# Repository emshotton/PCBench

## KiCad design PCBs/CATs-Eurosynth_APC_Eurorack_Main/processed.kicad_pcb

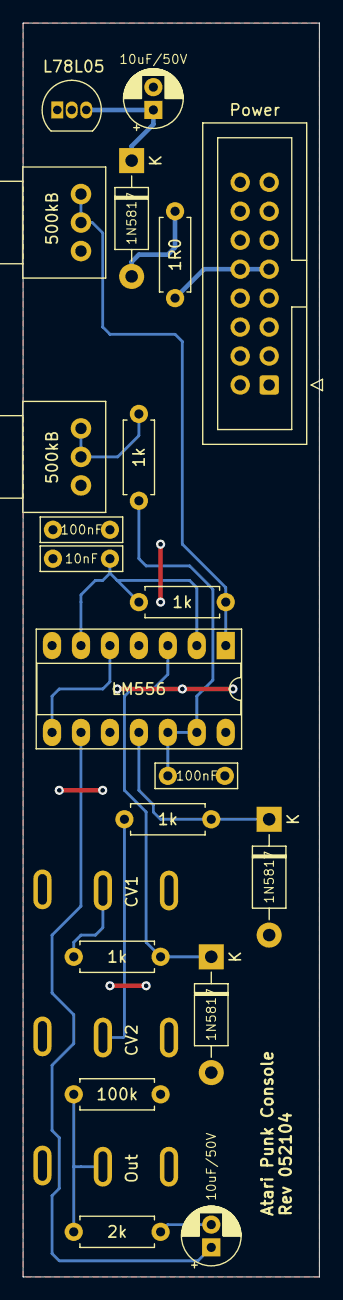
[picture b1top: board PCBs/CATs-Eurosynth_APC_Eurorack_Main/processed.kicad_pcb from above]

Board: 2 copper layers, 26.0 x 110.0 mm, 23 parts (0 on the bottom side), 17 nets.

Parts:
C1: 10nF; C_Rect_L7.0mm_W2.0mm_P5.00mm
C2, C4: 100nF; C_Rect_L7.0mm_W2.0mm_P5.00mm
C3, C5: 10uF/50V; CP_Radial_D5.0mm_P2.00mm
D1, D2, D3: 1N5817; D_DO-41_SOD81_P10.16mm_Horizontal
IC1: L78L05; TO-92_Inline
IC2: LM556; DIP-14_W7.62mm_Socket_LongPads
J1: Power; IDC-Header_2x08_P2.54mm_Vertical
J4: Out; PJ-323
J5: CV2; PJ-323
J6: CV1; PJ-323
R1, R7, R8, R9: 1k; R_Axial_DIN0207_L6.3mm_D2.5mm_P7.62mm_Horizontal
R2: 1R0; R_Axial_DIN0207_L6.3mm_D2.5mm_P7.62mm_Horizontal
R3: 100k; R_Axial_DIN0207_L6.3mm_D2.5mm_P7.62mm_Horizontal
R4: 2k; R_Axial_DIN0207_L6.3mm_D2.5mm_P7.62mm_Horizontal
R10, R11: 500kB; Potentiometer_Alps_RK097_Single_Horizontal

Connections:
+12V: J1.9, J1.10, R2.2
+VDC: C4.1, IC1.1, IC2.4, IC2.10, IC2.14, R10.3, R11.3
GND: C1.2, C2.2, C4.2, C5.2, D2.2, D3.2, IC1.2, IC2.7, J1.3, J1.4, J1.5, J1.6, J1.7, J1.8, J4.S, J5.S, J6.S, R3.1
unnamed: C1.1, IC2.2, IC2.6, R1.2
unnamed: C2.1, IC2.12, IC2.13, R9.1
unnamed: C3.1, IC2.9
unnamed: C3.2, R4.2
unnamed: C5.1, D1.1, IC1.3
unnamed: D1.2, R2.1
unnamed: D2.1, IC2.3, R7.2
unnamed: D3.1, IC2.11, R8.2
unnamed: IC2.1, R1.1, R10.1, R10.2
unnamed: IC2.5, IC2.8
unnamed: J4.T, R3.2, R4.1
unnamed: J5.T, R8.1
unnamed: J6.T, R7.1
unnamed: R9.2, R11.1, R11.2

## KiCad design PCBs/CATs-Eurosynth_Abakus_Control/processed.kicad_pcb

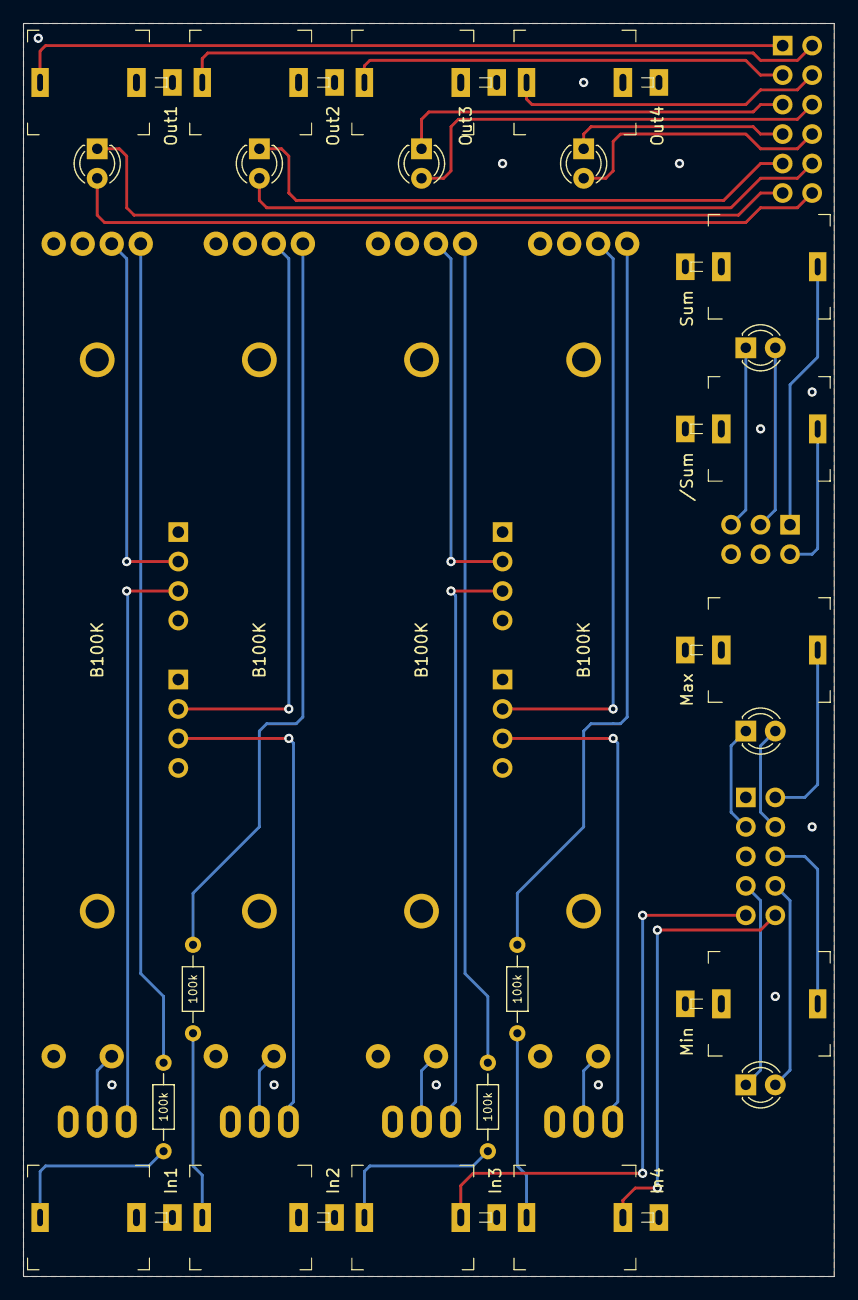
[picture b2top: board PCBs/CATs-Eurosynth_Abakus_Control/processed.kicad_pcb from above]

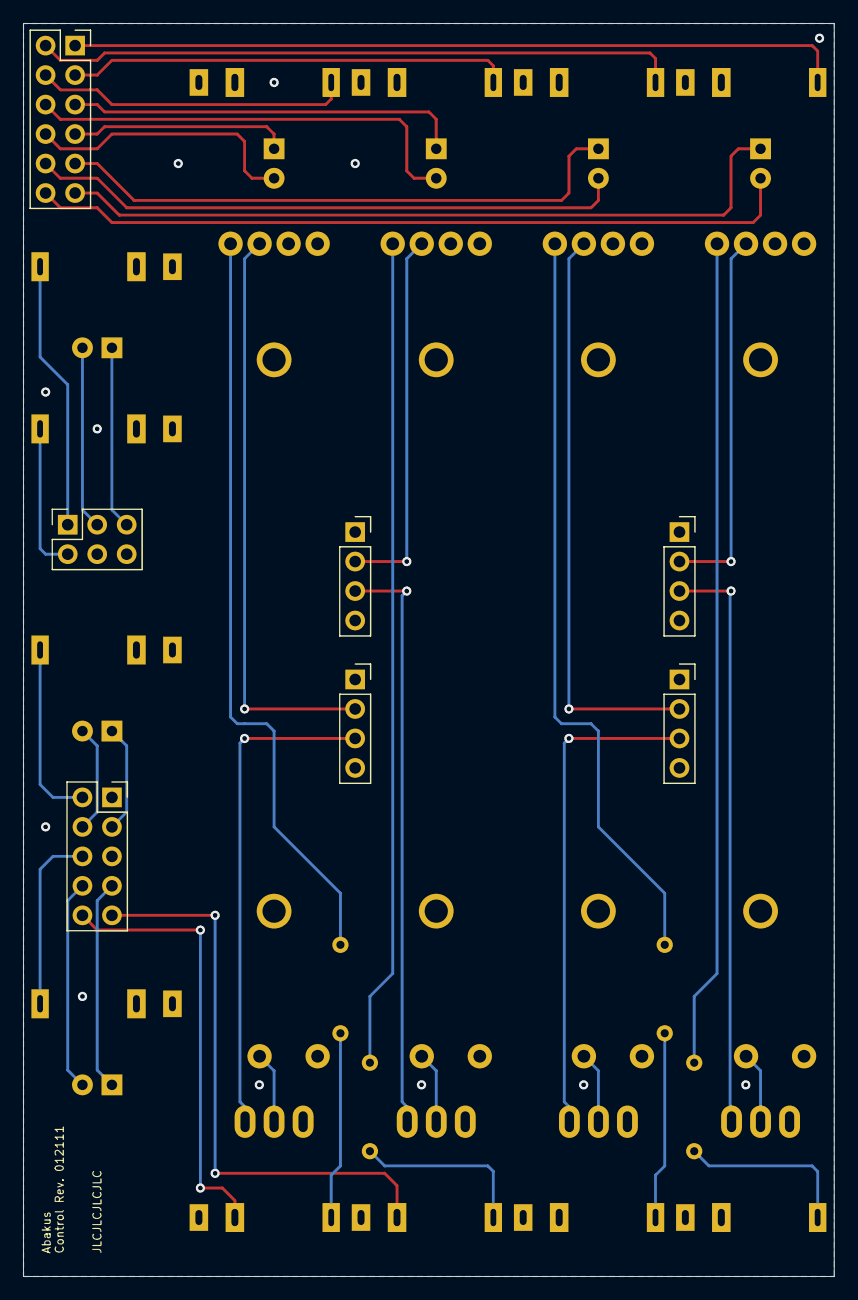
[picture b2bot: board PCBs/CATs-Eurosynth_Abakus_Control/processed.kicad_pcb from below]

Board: 2 copper layers, 69.8 x 108.0 mm, 38 parts (7 on the bottom side), 45 nets.

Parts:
D1: Out1; LED_D3.0mm
D2: Out2; LED_D3.0mm
D3: Out3; LED_D3.0mm
D4: Out4; LED_D3.0mm
D5: Min; LED_D3.0mm
D6: Sum; LED_D3.0mm
D7: Max; LED_D3.0mm
J1: In1; Jack_3.5mm_QingPu_WQP-PJ301M-12
J2: In2; Jack_3.5mm_QingPu_WQP-PJ301M-12
J3: In3; Jack_3.5mm_QingPu_WQP-PJ301M-12
J4: In4; Jack_3.5mm_QingPu_WQP-PJ301M-12
J5: Out1; Jack_3.5mm_QingPu_WQP-PJ301M-12
J6: Out2; Jack_3.5mm_QingPu_WQP-PJ301M-12
J7: Out3; Jack_3.5mm_QingPu_WQP-PJ301M-12
J8: Out4; Jack_3.5mm_QingPu_WQP-PJ301M-12
J9: /Sum; Jack_3.5mm_QingPu_WQP-PJ301M-12
J10: Sum; Jack_3.5mm_QingPu_WQP-PJ301M-12
J11: Max; Jack_3.5mm_QingPu_WQP-PJ301M-12
J12: Min; Jack_3.5mm_QingPu_WQP-PJ301M-12
J13: Out; PinSocket_2x06_P2.54mm_Vertical
J14: In1; PinSocket_1x04_P2.54mm_Vertical
J15: In2; PinSocket_1x04_P2.54mm_Vertical
J16: In3; PinSocket_1x04_P2.54mm_Vertical
J17: In4; PinSocket_1x04_P2.54mm_Vertical
J18: Sum; PinSocket_2x03_P2.54mm_Vertical
J19: MinMax; PinSocket_2x05_P2.54mm_Vertical
P1, P2, P3, P4: B100K; Potentiometer_AlpsAlpine_RS6011YA9A07
R1, R2, R3, R4: 100k; R_Axial_DIN0204_L3.6mm_D1.6mm_P7.62mm_Horizontal
SW1: Att/AV1; SMTS-102-2xxx
SW2: Att/AV2; SMTS-102-2xxx
SW3: Att/AV3; SMTS-102-2xxx
SW4: Att/AV4; SMTS-102-2xxx

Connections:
+5V: J3.TN, J19.9
+10V: J4.TN, J19.10
+In1: J14.2, P1.CW
+In2: J15.2, P2.CW
+In3: J16.2, P3.CW
+In4: J17.2, P4.CW
-In1: J14.3, SW1.1
-In2: J15.3, SW2.1
-In3: J16.3, SW3.1
-In4: J17.3, SW4.1
GND: J1.S, J1.TN, J2.S, J2.TN, J3.S, J4.S, J5.S, J6.S, J7.S, J8.S, J9.S, J10.S, J11.S, J12.S, J14.1, J14.4, J15.1, J15.4, J16.1, J16.4, J17.1, J17.4, J18.4, J18.6, J19.1, J19.5, SW1.3, SW2.3, SW3.3, SW4.3
Inv_Sum: J9.T, J18.2
LED_Max_1: D7.1, J19.3
LED_Max_2: D7.2, J19.4
LED_Min_1: D5.1, J19.7
LED_Min_2: D5.2, J19.8
LED_Out_1_1: D1.1, J13.11
LED_Out_1_2: D1.2, J13.12
LED_Out_2_1: D2.1, J13.9
LED_Out_2_2: D2.2, J13.10
LED_Out_3_1: D3.1, J13.5
LED_Out_3_2: D3.2, J13.6
LED_Out_4_1: D4.1, J13.7
LED_Out_4_2: D4.2, J13.8
LED_Sum_1: D6.1, J18.5
LED_Sum_2: D6.2, J18.3
Max: J11.T, J19.2
Min: J12.T, J19.6
unnamed: J1.T, R1.2
unnamed: J2.T, R2.2
unnamed: J3.T, R3.2
unnamed: J4.T, R4.2
unnamed: P1.CCW, SW1.2
unnamed: P1.W, R1.1
unnamed: P2.CCW, SW2.2
unnamed: P2.W, R2.1
unnamed: P3.CCW, SW3.2
unnamed: P3.W, R3.1
unnamed: P4.CCW, SW4.2
unnamed: P4.W, R4.1
Out1: J5.T, J13.1
Out2: J6.T, J13.2
Out3: J7.T, J13.3
Out4: J8.T, J13.4
Sum: J10.T, J18.1

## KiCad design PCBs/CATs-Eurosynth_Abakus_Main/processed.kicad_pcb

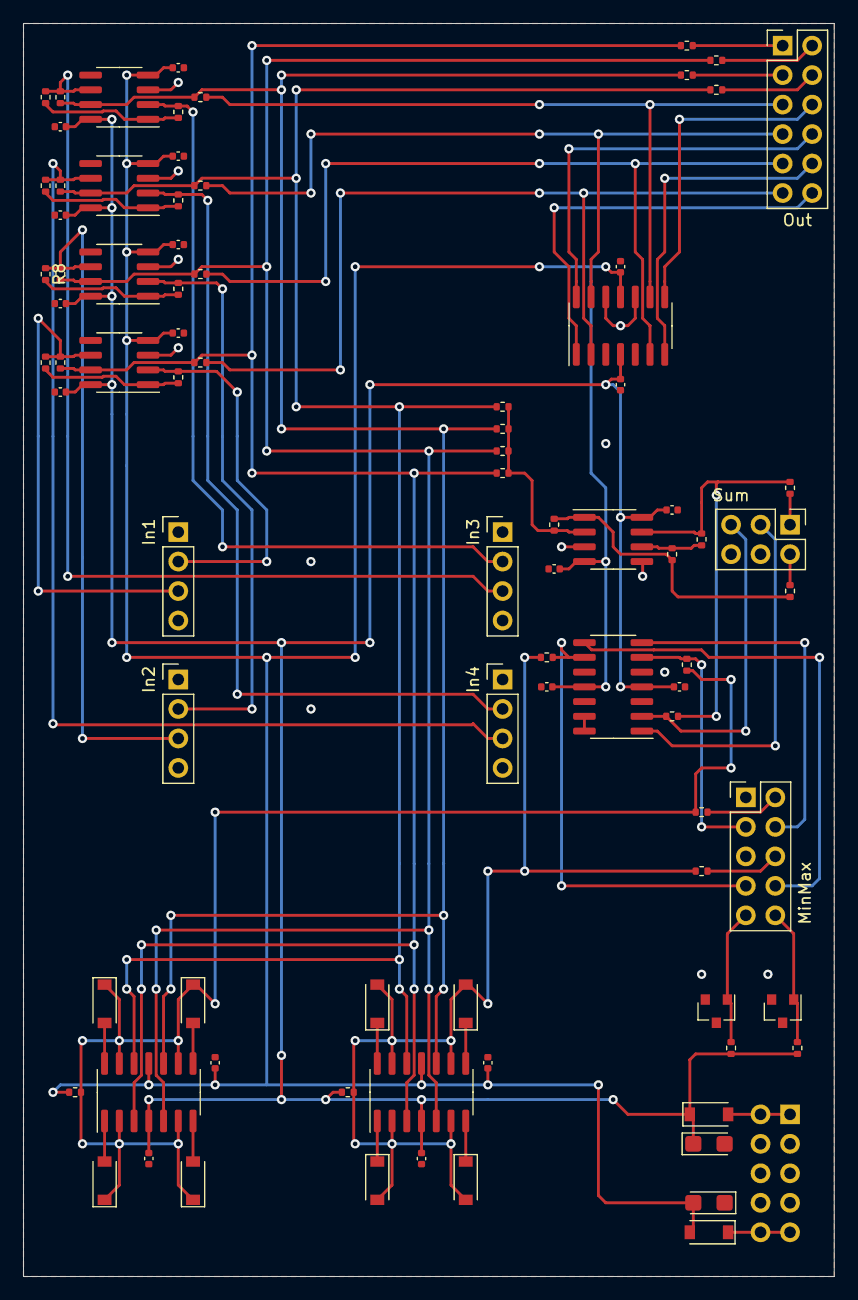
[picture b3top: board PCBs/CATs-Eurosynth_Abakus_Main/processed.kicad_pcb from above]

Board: 2 copper layers, 69.8 x 108.0 mm, 87 parts (1 on the bottom side), 60 nets.

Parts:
C1, C2: 10µ; CP_EIA-3216-18_Kemet-A
C3, C4, C5, C6, C7, C8, C9, C10, C11, C12, C13, C14, C15, C16, C17, C18, C19, C20: 100n; C_0402_1005Metric
D1, D2: B5817W; D_SOD-123
D3, D4, D5, D6, D7, D8, D9, D10: 1N4148W; D_SOD-123
J1: Power; Power_2x5_Vertical
J2: Out; PinHeader_2x06_P2.54mm_Vertical
J3: In1; PinHeader_1x04_P2.54mm_Vertical
J4: In2; PinHeader_1x04_P2.54mm_Vertical
J5: In3; PinHeader_1x04_P2.54mm_Vertical
J6: In4; PinHeader_1x04_P2.54mm_Vertical
J7: Sum; PinHeader_2x03_P2.54mm_Vertical
J8: MinMax; PinHeader_2x05_P2.54mm_Vertical
R1, R2, R3, R4, R7, R8, R9, R10, R11, R12, R13, R14, R21, R22, R23, R24, R27, R29, R30: 100k; R_0402_1005Metric
R5, R6, R15, R16, R17, R18, R19, R20, R25, R26, R28, R31, R32, R34, R36, R37, R38: 1k; R_0402_1005Metric
R33, R35: 10k; R_0402_1005Metric
U1, U2, U3, U4, U5: TL072CDT; SOIC-8_3.9x4.9mm_P1.27mm
U6, U7, U8, U9: TL074CDR; SOIC-14_3.9x8.7mm_P1.27mm
U10: LM4040AIM3-5.0/NOPB; SOT-23
U11: LM4040C10IDBZR; SOT-23

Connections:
+5V: J8.9, R37.1, U10.1
+10V: J8.10, R38.1, U11.1
+12V: C1.1, C3.1, C5.1, C7.1, C9.1, C11.1, C13.1, C15.1, C17.1, C19.1, D1.1, R35.2, R37.2, R38.2, U1.8, U2.8, U3.8, U4.8, U5.8, U6.4, U7.4, U8.4, U9.4
+In1: J3.2, R1.2, U1.2
+In2: J4.2, R2.2, U2.2
+In3: J5.2, R3.2, U3.2
+In4: J6.2, R4.2, U4.2
-12V: C2.2, C4.2, C6.2, C8.2, C10.2, C12.2, C14.2, C16.2, C18.2, C20.2, D2.2, R33.1, U1.4, U2.4, U3.4, U4.4, U5.4, U6.11, U7.11, U8.11, U9.11
-In1: J3.3, R7.1, R11.2, U1.6
-In2: J4.3, R8.1, R12.2, U2.6
-In3: J5.3, R9.1, R13.2, U3.6
-In4: J6.3, R10.1, R14.2, U4.6
GND: C1.2, C2.1, C3.2, C4.1, C5.2, C6.1, C7.2, C8.1, C9.2, C10.1, C11.2, C12.1, C13.2, C14.1, C15.2, C16.1, C17.2, C18.1, C19.2, C20.1, J1.GND, J3.1, J3.4, J4.1, J4.4, J5.1, J5.4, J6.1, J6.4, J7.4, J7.6, J8.1, J8.5, U1.3, U1.5, U2.3, U2.5, U3.3, U3.5, U4.3, U4.5, U5.3, U5.5, U8.3, U8.5, U8.10, U8.12, U9.3, U9.5, U9.10, U9.12, U10.2, U11.2
Int_Inv_Sum: R27.1, R28.2, R29.2, U5.1
Int_Max: D3.1, D4.1, D5.1, D6.1, R31.2, R33.2, R34.2, U6.2, U6.6, U6.9, U6.13
Int_Min: D7.2, D8.2, D9.2, D10.2, R26.2, R35.1, R36.2, U7.2, U7.6, U7.9, U7.13
Int_Out1: R5.2, R11.1, R17.2, R21.2, U1.7, U6.3, U7.3
Int_Out2: R12.1, R15.2, R18.2, R22.2, U2.7, U6.5, U7.5
Int_Out3: R6.2, R13.1, R19.2, R23.2, U3.7, U6.10, U7.10
Int_Out4: R14.1, R16.2, R20.2, R24.2, U4.7, U6.12, U7.12
Int_Sum: R25.2, R30.1, R32.2, U5.7
Inv_Sum: J7.2, R28.1
LED_Max_1: J8.3, R31.1, U9.6
LED_Max_2: J8.4, U9.7
LED_Min_1: J8.7, R26.1, U9.9
LED_Min_2: J8.8, U9.8
LED_Out_1_1: J2.11, R5.1, U8.2
LED_Out_1_2: J2.12, U8.1
LED_Out_2_1: J2.9, R15.1, U8.6
LED_Out_2_2: J2.10, U8.7
LED_Out_3_1: J2.5, R6.1, U8.9
LED_Out_3_2: J2.6, U8.8
LED_Out_4_1: J2.7, R16.1, U8.13
LED_Out_4_2: J2.8, U8.14
LED_Sum_1: J7.5, R25.1, U9.2
LED_Sum_2: J7.3, U9.1
Max: J8.2, R34.1
Min: J8.6, R36.1
unnamed: D1.2, J1.+12V
unnamed: D2.1, J1.-12V
unnamed: D3.2, U6.1
unnamed: D4.2, U6.7
unnamed: D5.2, U6.8
unnamed: D6.2, U6.14
unnamed: D7.1, U7.1
unnamed: D8.1, U7.7
unnamed: D9.1, U7.8
unnamed: D10.1, U7.14
unnamed: R1.1, R7.2, U1.1
unnamed: R2.1, R8.2, U2.1
unnamed: R3.1, R9.2, U3.1
unnamed: R4.1, R10.2, U4.1
unnamed: R21.1, R22.1, R23.1, R24.1, R27.2, U5.2
unnamed: R29.1, R30.2, U5.6
unnamed: U9.13, U9.14
Out1: J2.1, R17.1
Out2: J2.2, R18.1
Out3: J2.3, R19.1
Out4: J2.4, R20.1
Sum: J7.1, R32.1

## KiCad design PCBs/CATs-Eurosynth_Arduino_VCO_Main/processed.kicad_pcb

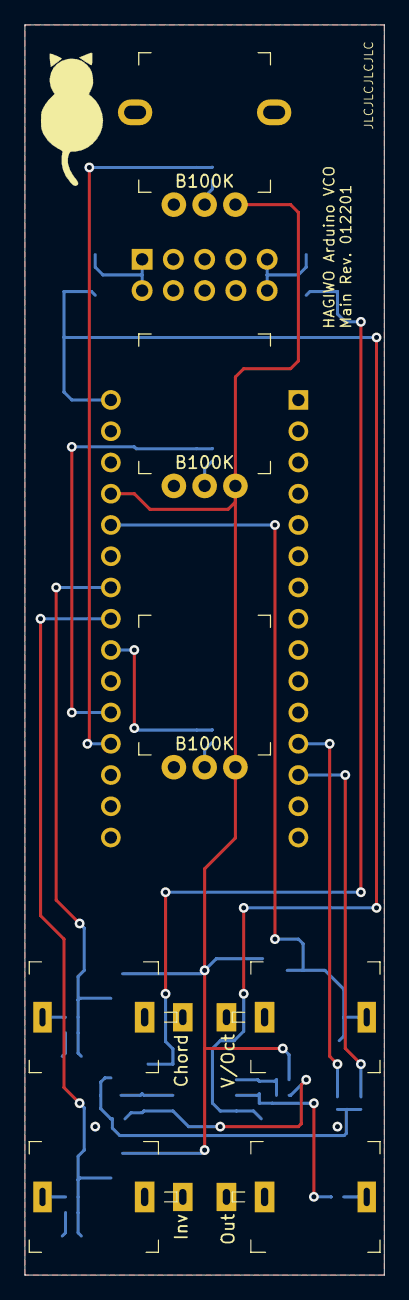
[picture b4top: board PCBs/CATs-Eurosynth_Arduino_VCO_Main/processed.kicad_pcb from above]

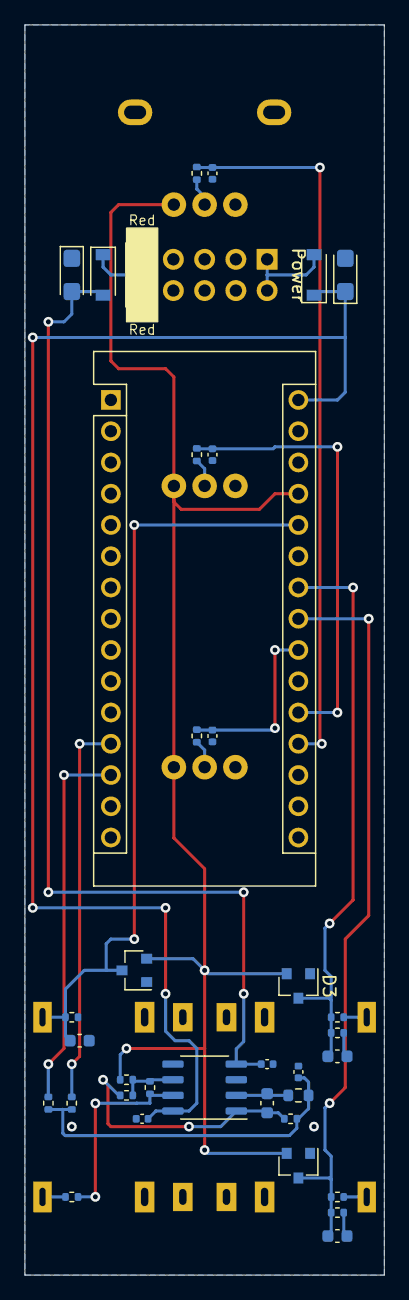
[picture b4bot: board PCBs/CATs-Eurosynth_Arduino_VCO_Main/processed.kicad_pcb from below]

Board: 2 copper layers, 29.2 x 101.6 mm, 43 parts (36 on the bottom side), 25 nets.

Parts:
A1: Arduino_Nano_v3.x; Arduino_Nano
C1, C11: 10µ; CP_EIA-3216-18_Kemet-A
C2, C3, C4: 10n; C_0402_1005Metric
C5, C7, C9: 68n; C_0603_1608Metric
C6: 3.3n; C_0603_1608Metric
C8: 22n; C_0402_1005Metric
C10, C12: 100n; C_0402_1005Metric
D1, D6: B5819W SL; D_SOD-123
D2, D3, D4: BAV99; SOT-23
J1: Power; Power_2x5_Vertical
J2: V/Oct; Jack_3.5mm_QingPu_WQP-PJ301M-12
J3: Inv; Jack_3.5mm_QingPu_WQP-PJ301M-12
J4: Out; Jack_3.5mm_QingPu_WQP-PJ301M-12
J5: Chord; Jack_3.5mm_QingPu_WQP-PJ301M-12
P1: B100K; Potentiometer_AlpsAlpine_RK09L1140
P2, P3: B100K; Potentiometer_AlpsAlpine_RK09L1140_oS
R1, R2, R3, R9, R12, R15: 1k; R_0402_1005Metric
R4, R8, R10, R11, R14, R16: 100k; R_0402_1005Metric
R5: 499k; R_0402_1005Metric
R6: 3k9; R_0402_1005Metric
R7: 7k5; R_0402_1005Metric
R13: 2k7; R_0603_1608Metric
U1: TL072CDT; SO-8_3.9x4.9mm_P1.27mm

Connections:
+5V: A1.27, D2.2, D3.2, D4.2, P1.CW, P2.CW, P3.CW, R16.2
+12V: A1.30, C1.1, C10.1, D1.1, U1.8
-12V: C11.2, C12.2, D6.2, U1.4
A0: A1.19, C2.1, R1.1
A1: A1.20, C3.1, R2.1
A3: A1.22, C4.1, R3.1
A4: A1.23, C7.1, D2.3, R8.1, R9.2
A5: A1.24, C9.1, D3.3, R11.1, R12.2
A7: A1.26, C5.1, D4.3, J2.T, R4.1
D9: A1.12, R6.2
D10: A1.13, R5.2
GND: A1.4, A1.29, C1.2, C2.2, C3.2, C4.2, C5.2, C7.2, C8.2, C9.2, C10.2, C11.1, C12.1, D2.1, D3.1, D4.1, J1.GND, J2.S, J2.TN, J3.S, J3.TN, J4.S, J5.S, J5.TN, P1.CCW, P2.CCW, P3.CCW, R4.2, R8.2, R11.2, U1.3, U1.5
unnamed: C6.1, R7.2, R14.2, U1.1
unnamed: C6.2, R13.1, U1.2
unnamed: C8.1, R5.1, R6.1, R7.1, R13.2
unnamed: D1.2, J1.+12V
unnamed: D6.1, J1.-12V
unnamed: J3.T, R9.1
unnamed: J4.T, R15.1
unnamed: J5.T, R12.1
unnamed: P1.W, R1.2
unnamed: P2.W, R2.2
unnamed: P3.W, R3.2
unnamed: R10.1, R15.2, U1.7
unnamed: R10.2, R14.1, R16.1, U1.6

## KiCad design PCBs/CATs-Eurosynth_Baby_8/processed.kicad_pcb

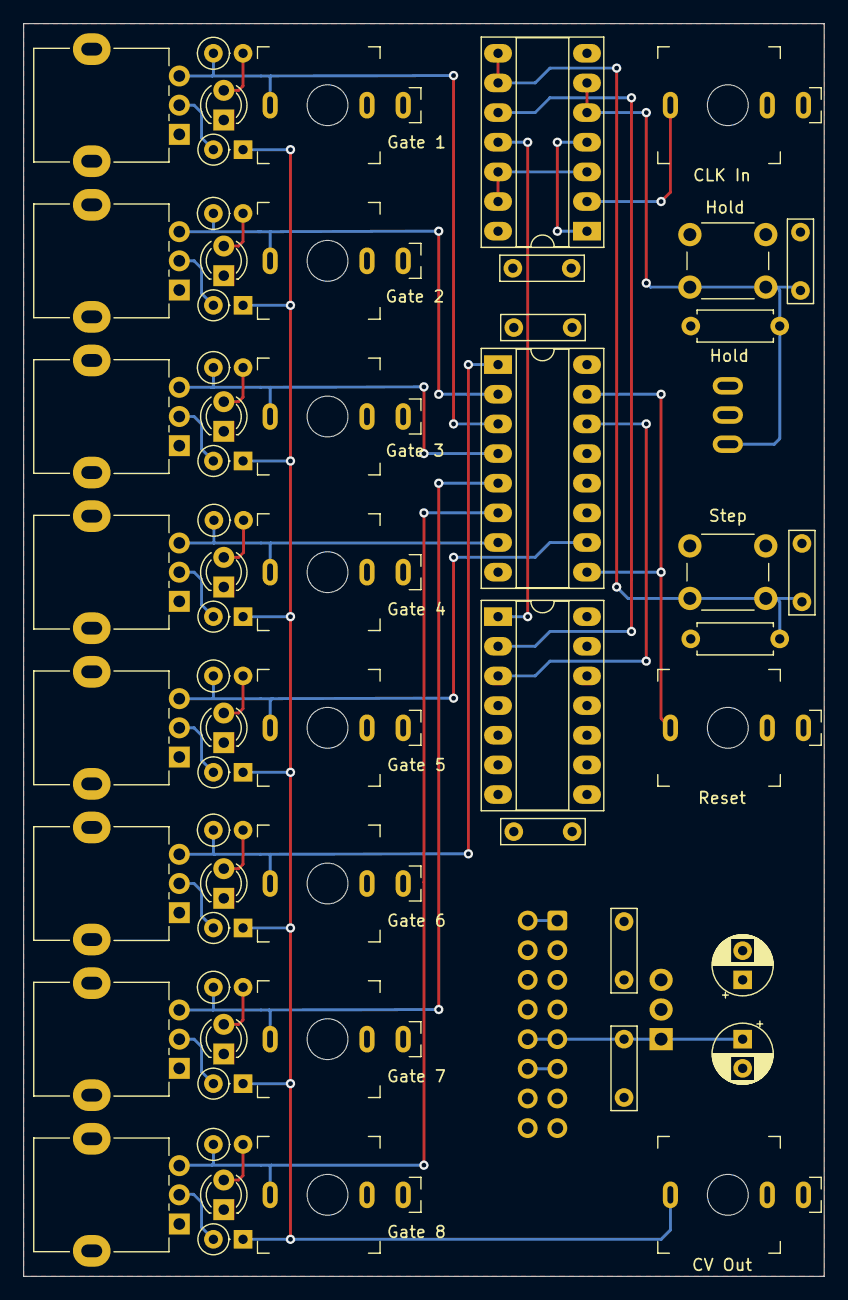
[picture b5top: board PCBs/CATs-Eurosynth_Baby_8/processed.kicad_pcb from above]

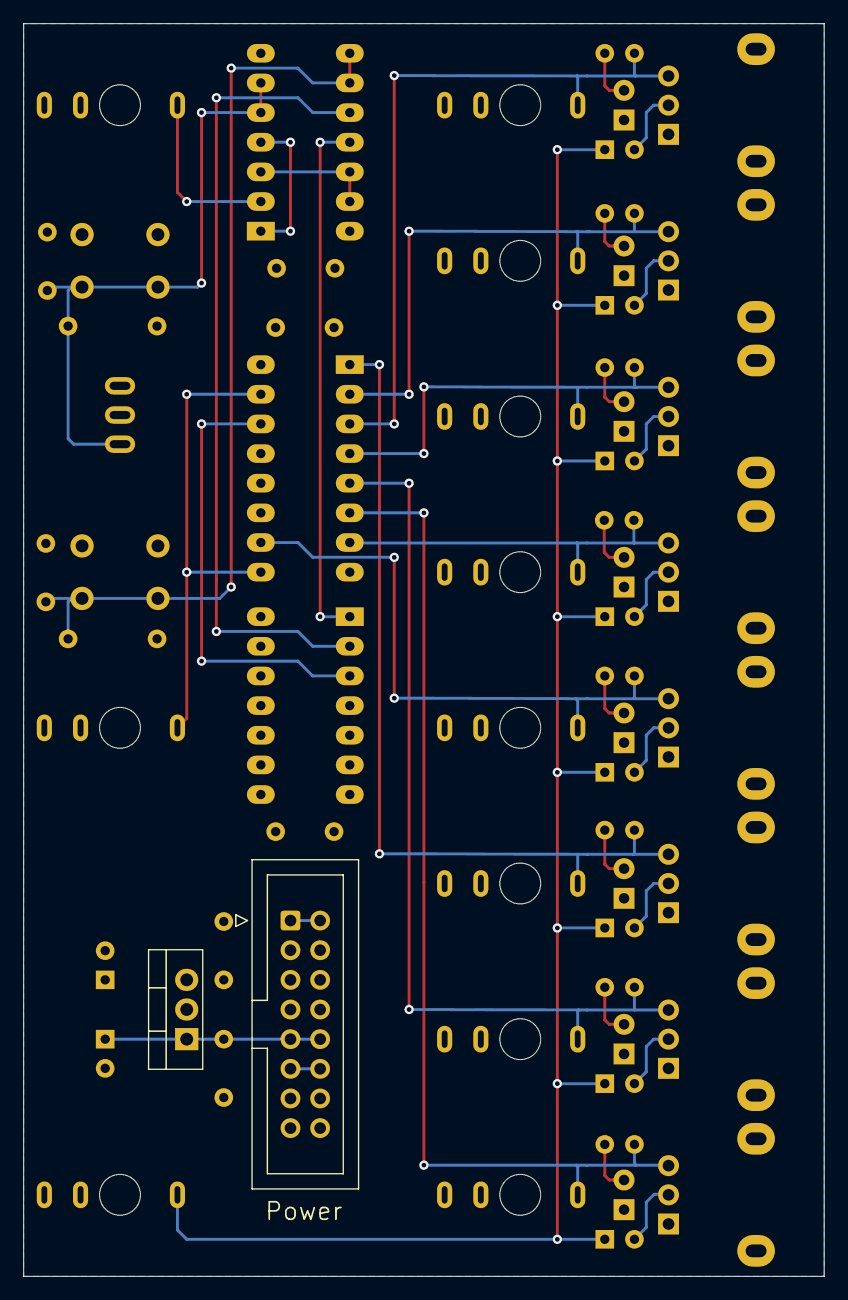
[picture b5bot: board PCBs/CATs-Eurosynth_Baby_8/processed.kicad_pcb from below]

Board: 2 copper layers, 68.6 x 107.3 mm, 62 parts (2 on the bottom side), 39 nets.

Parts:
C1, C2, C3, C4, C5, C6, C7: 100nF; C_Rect_L7.0mm_W2.0mm_P5.00mm
C8, C9: 10µF/50V; CP_Radial_D5.0mm_P2.50mm
D1, D2, D3, D4, D5, D6, D7, D8: 1N4148; D_DO-35_SOD27_P2.54mm_Vertical_KathodeUp
D9, D10, D11, D12, D13, D14, D15, D16: LED; LED_D3.0mm
J1: Power; IDC-Header_2x08_P2.54mm_Vertical
J2: CV Out; PJ-301-M-12
J3: CLK In; PJ-301-M-12
J4: Reset; PJ-301-M-12
J5: Gate 1; PJ-301-M-12
J6: Gate 2; PJ-301-M-12
J7: Gate 3; PJ-301-M-12
J8: Gate 4; PJ-301-M-12
J9: Gate 5; PJ-301-M-12
J10: Gate 6; PJ-301-M-12
J11: Gate 7; PJ-301-M-12
J12: Gate 8; PJ-301-M-12
R1, R2: 100k; R_Axial_DIN0207_L6.3mm_D2.5mm_P7.62mm_Horizontal
R3, R4, R5, R6, R7, R8, R9, R10: 120R; R_Axial_DIN0207_L6.3mm_D2.5mm_P2.54mm_Vertical
RV1, RV2, RV3, RV4, RV5, RV6, RV7, RV8: 500kB; Potentiometer_Alpha_RD901F-40-00D_Single_Vertical
SW1: Hold; SMTS-1xx-Solder
SW2: Hold; SW_PUSH_6mm_H13mm
SW3: Step; SW_PUSH_6mm_H13mm
U1: 4093; DIP-14_W7.62mm_Socket_LongPads
U2: 4030; DIP-14_W7.62mm_Socket_LongPads
U3: 4017; DIP-16_W7.62mm_Socket_LongPads
U4: LM7809_TO220; TO-220-3_Vertical

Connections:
+5V: J1.11, J1.12
+9V: C4.1, C5.1, C6.1, C7.1, C9.1, R1.1, R2.1, U1.14, U2.14, U3.16, U4.3
+12V: C3.1, C8.1, J1.9, J1.10, U4.1
-12V: J1.1, J1.2
CLOCK: J3.T, U1.2
CV: D1.1, D2.1, D3.1, D4.1, D5.1, D6.1, D7.1, D8.1, J2.T
GND: C1.2, C2.2, C3.2, C4.2, C5.2, C6.2, C7.2, C8.2, C9.2, D9.1, D10.1, D11.1, D12.1, D13.1, D14.1, D15.1, D16.1, J1.3, J1.4, J1.5, J1.6, J1.7, J1.8, J2.S, J3.S, J4.S, J5.S, J6.S, J7.S, J8.S, J9.S, J10.S, J11.S, J12.S, RV1.1, RV2.1, RV3.1, RV4.1, RV5.1, RV6.1, RV7.1, RV8.1, SW1.1, SW2.1, SW3.1, U1.7, U2.7, U3.8, U3.13, U4.2
HOLD: U1.1, U1.4
unnamed: C1.1, R1.2, SW1.2, SW2.2, U1.5, U1.6
unnamed: C2.1, R2.2, SW3.2, U1.8, U1.9
unnamed: D1.2, RV1.2
unnamed: D2.2, RV2.2
unnamed: D3.2, RV3.2
unnamed: D4.2, RV4.2
unnamed: D5.2, RV5.2
unnamed: D6.2, RV6.2
unnamed: D7.2, RV7.2
unnamed: D8.2, RV8.2
unnamed: D9.2, R3.2
unnamed: D10.2, R4.2
unnamed: D11.2, R5.2
unnamed: D12.2, R6.2
unnamed: D13.2, R7.2
unnamed: D14.2, R8.2
unnamed: D15.2, R9.2
unnamed: D16.2, R10.2
unnamed: J5.T, R3.1, RV1.3, U3.3
unnamed: J6.T, R4.1, RV2.3, U3.2
unnamed: J7.T, R5.1, RV3.3, U3.4
unnamed: J8.T, R6.1, RV4.3, U3.7
unnamed: J9.T, R7.1, RV5.3, U3.10
unnamed: J10.T, R8.1, RV6.3, U3.1
unnamed: J11.T, R9.1, RV7.3, U3.5
unnamed: J12.T, R10.1, RV8.3, U3.6
unnamed: U1.11, U2.1
unnamed: U1.3, U1.12, U1.13
unnamed: U2.3, U3.14
RESET: J4.T, U3.9, U3.15
STEP: U1.10, U2.2

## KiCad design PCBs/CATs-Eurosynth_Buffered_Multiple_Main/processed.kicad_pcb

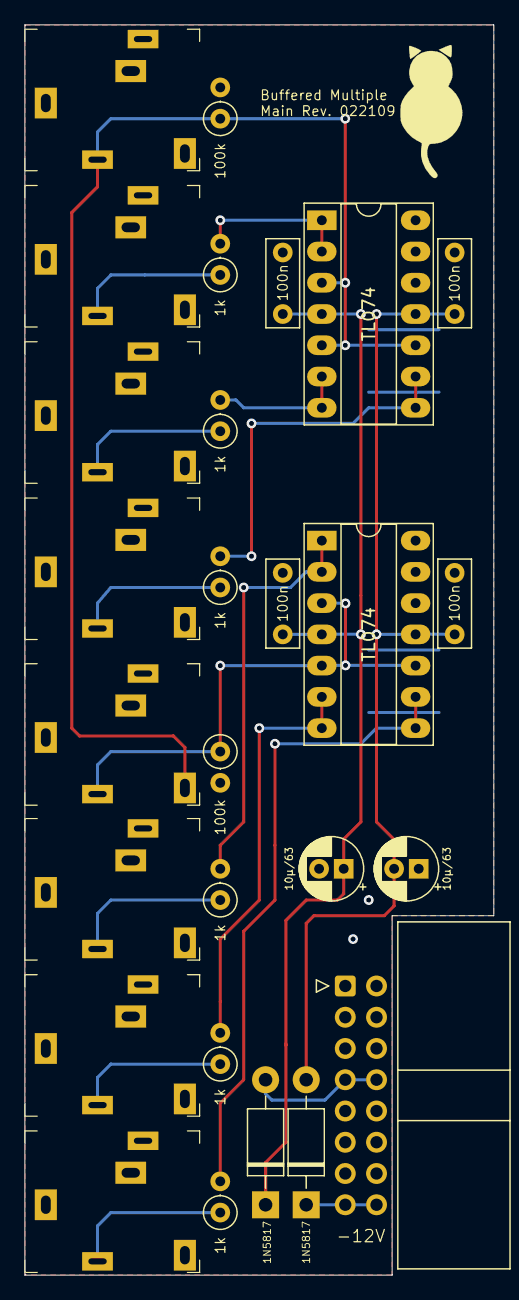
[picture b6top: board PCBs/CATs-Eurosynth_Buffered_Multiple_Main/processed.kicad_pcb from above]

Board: 2 copper layers, 38.1 x 101.6 mm, 27 parts (0 on the bottom side), 19 nets.

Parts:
C1, C2: 10µ/63; CP_Radial_D5.0mm_P2.00mm
C3, C4, C5, C6: 100n; C_Rect_L7.0mm_W2.5mm_P5.00mm
D1, D2: 1N5817; D_DO-41_SOD81_P10.16mm_Horizontal
J1: In 1; Jack_3.5mm_QingPu_WQP-PJ324M
J2: Power; IDC-Header_2x08_P2.54mm_Horizontal
J3: Out 1-1; Jack_3.5mm_QingPu_WQP-PJ324M
J4: Out 1-2; Jack_3.5mm_QingPu_WQP-PJ324M
J5: Out 2-1; Jack_3.5mm_QingPu_WQP-PJ324M
J6: Out 2-2; Jack_3.5mm_QingPu_WQP-PJ324M
J7: In 2; Jack_3.5mm_QingPu_WQP-PJ324M
J8: Out 1-3; Jack_3.5mm_QingPu_WQP-PJ324M
J9: Out 2-3; Jack_3.5mm_QingPu_WQP-PJ324M
R1, R6: 100k; R_Axial_DIN0207_L6.3mm_D2.5mm_P2.54mm_Vertical
R2, R3, R4, R5, R7, R8: 1k; R_Axial_DIN0207_L6.3mm_D2.5mm_P2.54mm_Vertical
U1, U2: TL074; DIP-14_W7.62mm_Socket_LongPads

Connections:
+12V: C1.1, C3.1, C5.1, D1.1, U1.4, U2.4
+12VA: D1.2, J2.7, J2.8
-12V: C2.2, C4.2, C6.2, D2.2, U1.11, U2.11
-12VA: D2.1, J2.15, J2.16
GND: C1.2, C2.1, C3.2, C4.1, C5.2, C6.1, J1.S, J2.9, J2.10, J2.11, J2.12, J2.13, J2.14, J3.S, J4.S, J5.S, J6.S, J7.S, J8.S, J9.S, R1.2, R6.2
unnamed: J1.T, J7.TN, R1.1, U1.3, U1.5, U1.10
unnamed: J3.T, R2.1
unnamed: J4.T, R3.1
unnamed: J5.T, R4.1
unnamed: J6.T, R5.1
unnamed: J7.T, R6.1, U2.3, U2.5, U2.10
unnamed: J8.T, R7.1
unnamed: J9.T, R8.1
unnamed: R2.2, U1.1, U1.2
unnamed: R3.2, U1.6, U1.7
unnamed: R4.2, U2.1, U2.2
unnamed: R5.2, U2.6, U2.7
unnamed: R7.2, U1.8, U1.9
unnamed: R8.2, U2.8, U2.9

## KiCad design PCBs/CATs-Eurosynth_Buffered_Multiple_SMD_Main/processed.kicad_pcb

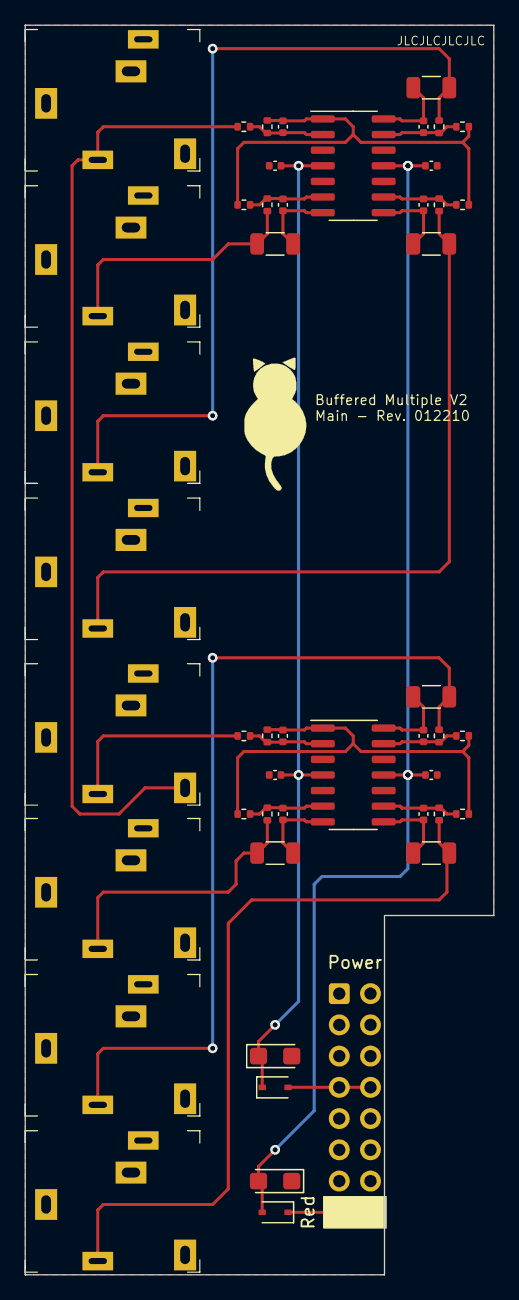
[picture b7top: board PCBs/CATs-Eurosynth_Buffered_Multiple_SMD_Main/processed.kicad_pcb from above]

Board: 2 copper layers, 38.1 x 101.6 mm, 49 parts (0 on the bottom side), 29 nets.

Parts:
C1, C2, C3, C4, C5, C6, C7, C8: 10p; C_0402_1005Metric
C9, C12: 10u/16; CP_EIA-3216-18_Kemet-A
C10, C11, C13, C14: 100n; C_0402_1005Metric
D1, D2: 1N5819WS; D_SOD-323
J1: In 1; Jack_3.5mm_QingPu_WQP-PJ324M
J2: In 2; Jack_3.5mm_QingPu_WQP-PJ324M
J3: Out 1-1; Jack_3.5mm_QingPu_WQP-PJ324M
J4: Out 2-1; Jack_3.5mm_QingPu_WQP-PJ324M
J5: Out 1-2; Jack_3.5mm_QingPu_WQP-PJ324M
J6: Out 2-2; Jack_3.5mm_QingPu_WQP-PJ324M
J7: Out 1-3; Jack_3.5mm_QingPu_WQP-PJ324M
J8: Out 2-3; Jack_3.5mm_QingPu_WQP-PJ324M
J9: Power; Power_2x8_Horizontal
R1, R2, R3, R4, R5, R6, R7, R8, R11, R12, R13, R14, R17, R18, R19, R20: 100k; R_0402_1005Metric
R9, R10, R15, R16, R21, R22: 1k; R_1206_3216Metric
U1, U2: TL074CDT; SOIC-14_3.9x8.7mm_P1.27mm

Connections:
+12V: C9.1, C10.2, C11.2, D1.1 (K), U1.4 (V+), U2.4 (V+)
-12V: C12.2, C13.1, C14.1, D2.2 (A), U1.11 (V-), U2.11 (V-)
GND: C9.2, C10.1, C11.1, C12.1, C13.2, C14.2, J1.S, J1.TN, J2.S, J3.S, J4.S, J5.S, J6.S, J7.S, J8.S, J9.GND, U1.3 (+), U1.5 (+), U1.10 (+), U1.12 (+), U2.3 (+), U2.5 (+), U2.10 (+), U2.12 (+)
unnamed: D1.2 (A), J9.+12V
unnamed: D2.1 (K), J9.-12V
unnamed: J1.T, J2.TN, R5.1
unnamed: J2.T, R6.1
unnamed: J3.T, R1.2, R9.2
unnamed: J4.T, R2.2, R10.2
unnamed: J5.T, R11.2, R15.2
unnamed: J6.T, R12.2, R16.2
unnamed: J7.T, R17.2, R21.2
unnamed: J8.T, R18.2, R22.2
unnamed: C1.2, R3.2, R7.1, R13.1, R19.1, U1.1
unnamed: C1.1, R3.1, R5.2, U1.2 (-)
unnamed: C3.1, R1.1, R7.2, U1.6 (-)
unnamed: C3.2, R9.1, U1.7
unnamed: C7.2, R21.1, U1.8
unnamed: C7.1, R17.1, R19.2, U1.9 (-)
unnamed: C5.1, R11.1, R13.2, U1.13 (-)
unnamed: C5.2, R15.1, U1.14
unnamed: C2.2, R4.2, R8.1, R14.1, R20.1, U2.1
unnamed: C2.1, R4.1, R6.2, U2.2 (-)
unnamed: C4.1, R2.1, R8.2, U2.6 (-)
unnamed: C4.2, R10.1, U2.7
unnamed: C8.2, R22.1, U2.8
unnamed: C8.1, R18.1, R20.2, U2.9 (-)
unnamed: C6.1, R12.1, R14.2, U2.13 (-)
unnamed: C6.2, R16.1, U2.14

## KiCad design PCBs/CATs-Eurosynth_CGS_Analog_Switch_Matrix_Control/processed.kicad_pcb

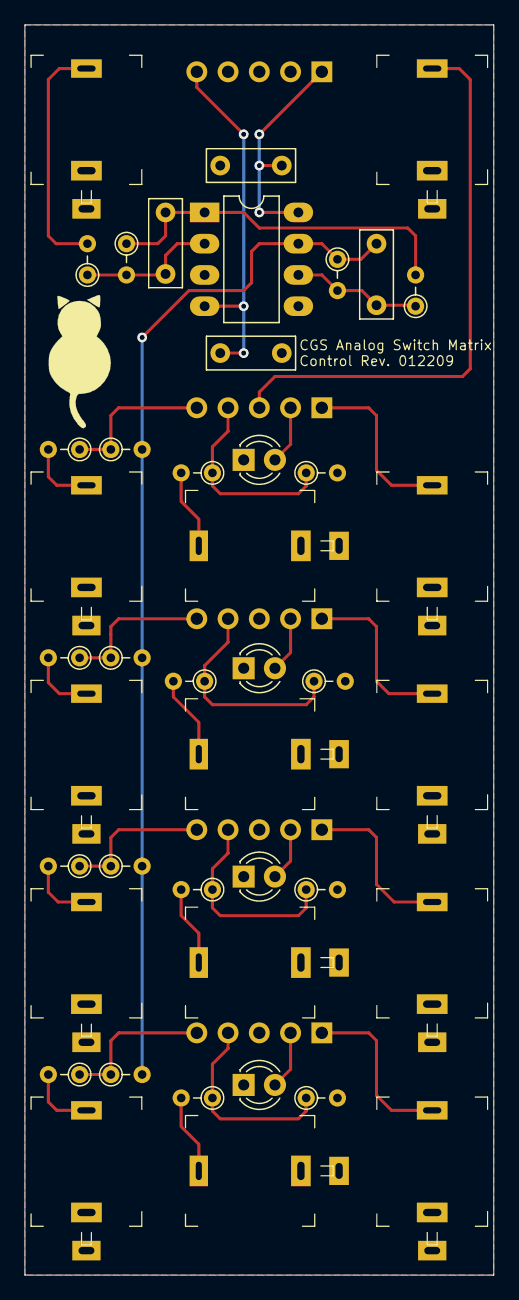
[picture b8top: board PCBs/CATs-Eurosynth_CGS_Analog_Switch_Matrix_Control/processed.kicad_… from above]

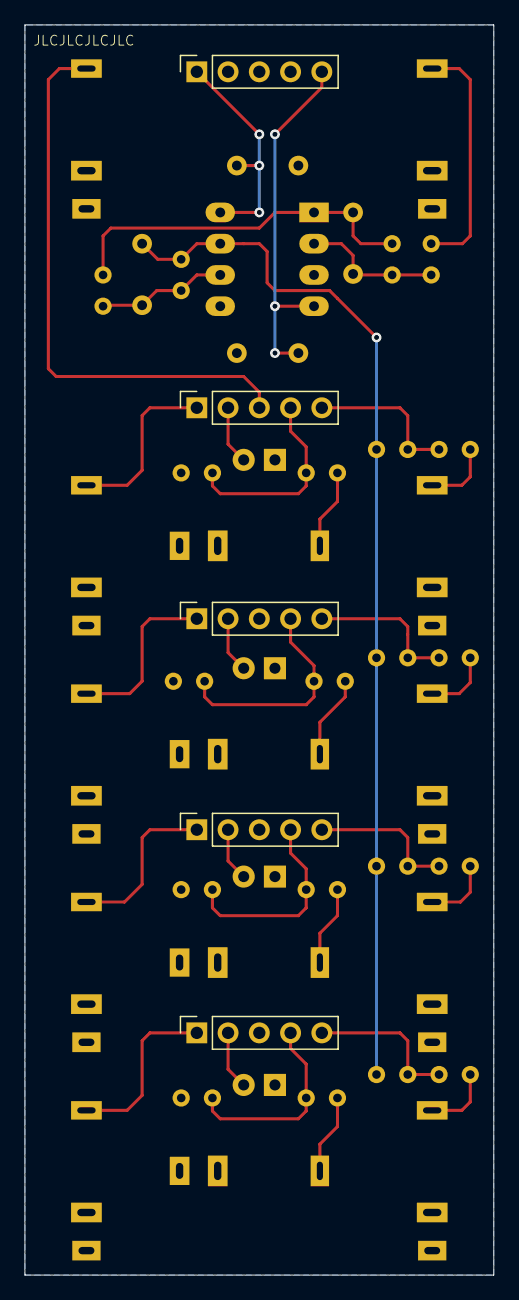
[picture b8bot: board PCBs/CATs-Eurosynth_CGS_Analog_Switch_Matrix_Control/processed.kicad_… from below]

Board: 2 copper layers, 38.1 x 101.6 mm, 48 parts (5 on the bottom side), 33 nets.

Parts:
C1, C2: 100n; C_Rect_L7.0mm_W2.5mm_P5.00mm
C3, C4: 47p; C_Rect_L7.0mm_W2.5mm_P5.00mm
D1, D2, D3, D4: Green; LED_D3.0mm
J1: Common In; Jack_3.5mm_QingPu_WQP-PJ301M-12
J2: In 1; Jack_3.5mm_QingPu_WQP-PJ301M-12
J3: In 2; Jack_3.5mm_QingPu_WQP-PJ301M-12
J4: In 3; Jack_3.5mm_QingPu_WQP-PJ301M-12
J5: In 4; Jack_3.5mm_QingPu_WQP-PJ301M-12
J6: Control 1; Jack_3.5mm_QingPu_WQP-PJ301M-12
J7: Control 2; Jack_3.5mm_QingPu_WQP-PJ301M-12
J8: Control 3; Jack_3.5mm_QingPu_WQP-PJ301M-12
J9: Control 4; Jack_3.5mm_QingPu_WQP-PJ301M-12
J10: Common Out; Jack_3.5mm_QingPu_WQP-PJ301M-12
J11: Out 1; Jack_3.5mm_QingPu_WQP-PJ301M-12
J12: Out 2; Jack_3.5mm_QingPu_WQP-PJ301M-12
J13: Out 3; Jack_3.5mm_QingPu_WQP-PJ301M-12
J14: Out 4; Jack_3.5mm_QingPu_WQP-PJ301M-12
J15: 1_COM; PinSocket_1x05_P2.54mm_Vertical
J16: 2; PinSocket_1x05_P2.54mm_Vertical
J17: 3; PinSocket_1x05_P2.54mm_Vertical
J18: 4; PinSocket_1x05_P2.54mm_Vertical
J19: POWER; PinSocket_1x05_P2.54mm_Vertical
R1, R2, R3, R4, R5, R6, R7, R8, R13, R14, R15, R16, R17, R18, R19, R20: 100k; R_Axial_DIN0204_L3.6mm_D1.6mm_P2.54mm_Vertical
R9, R10, R11, R12: 10k; R_Axial_DIN0204_L3.6mm_D1.6mm_P2.54mm_Vertical
U1: TL072; DIP-8_W7.62mm_LongPads

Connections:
+12V: C1.2, J19.1, U1.8
-12V: C2.1, J19.5, U1.4
C1: J15.4, R9.1, R13.1
C2: J16.4, R10.1, R14.1
C3: J17.4, R11.1, R15.1
C4: J18.4, R12.1, R16.1
COMIN: C4.1, R1.2, R3.2, R5.2, R7.2, R20.1, U1.7
COMOUT: J10.T, J15.3
GND: C1.1, C2.2, D1.1, D2.1, D3.1, D4.1, J1.S, J1.TN, J2.S, J2.TN, J3.S, J3.TN, J4.S, J4.TN, J5.S, J5.TN, J6.S, J6.TN, J7.S, J7.TN, J8.S, J8.TN, J9.S, J9.TN, J10.S, J11.S, J12.S, J13.S, J14.S, J16.3, J17.3, J18.3, J19.2, J19.3, J19.4, R13.2, R14.2, R15.2, R16.2, U1.3, U1.5
I1: J15.5, R1.1, R2.1
I2: J16.5, R3.1, R4.1
I3: J17.5, R5.1, R6.1
I4: J18.5, R7.1, R8.1
L1: D1.2, J15.2
L2: D2.2, J16.2
L3: D3.2, J17.2
L4: D4.2, J18.2
unnamed: C3.1, R18.1, R19.2, U1.1
unnamed: C3.2, R17.1, R18.2, U1.2
unnamed: C4.2, R19.1, R20.2, U1.6
unnamed: J1.T, R17.2
unnamed: J2.T, R2.2
unnamed: J3.T, R4.2
unnamed: J4.T, R6.2
unnamed: J5.T, R8.2
unnamed: J6.T, R9.2
unnamed: J7.T, R10.2
unnamed: J8.T, R11.2
unnamed: J9.T, R12.2
O1: J11.T, J15.1
O2: J12.T, J16.1
O3: J13.T, J17.1
O4: J14.T, J18.1
